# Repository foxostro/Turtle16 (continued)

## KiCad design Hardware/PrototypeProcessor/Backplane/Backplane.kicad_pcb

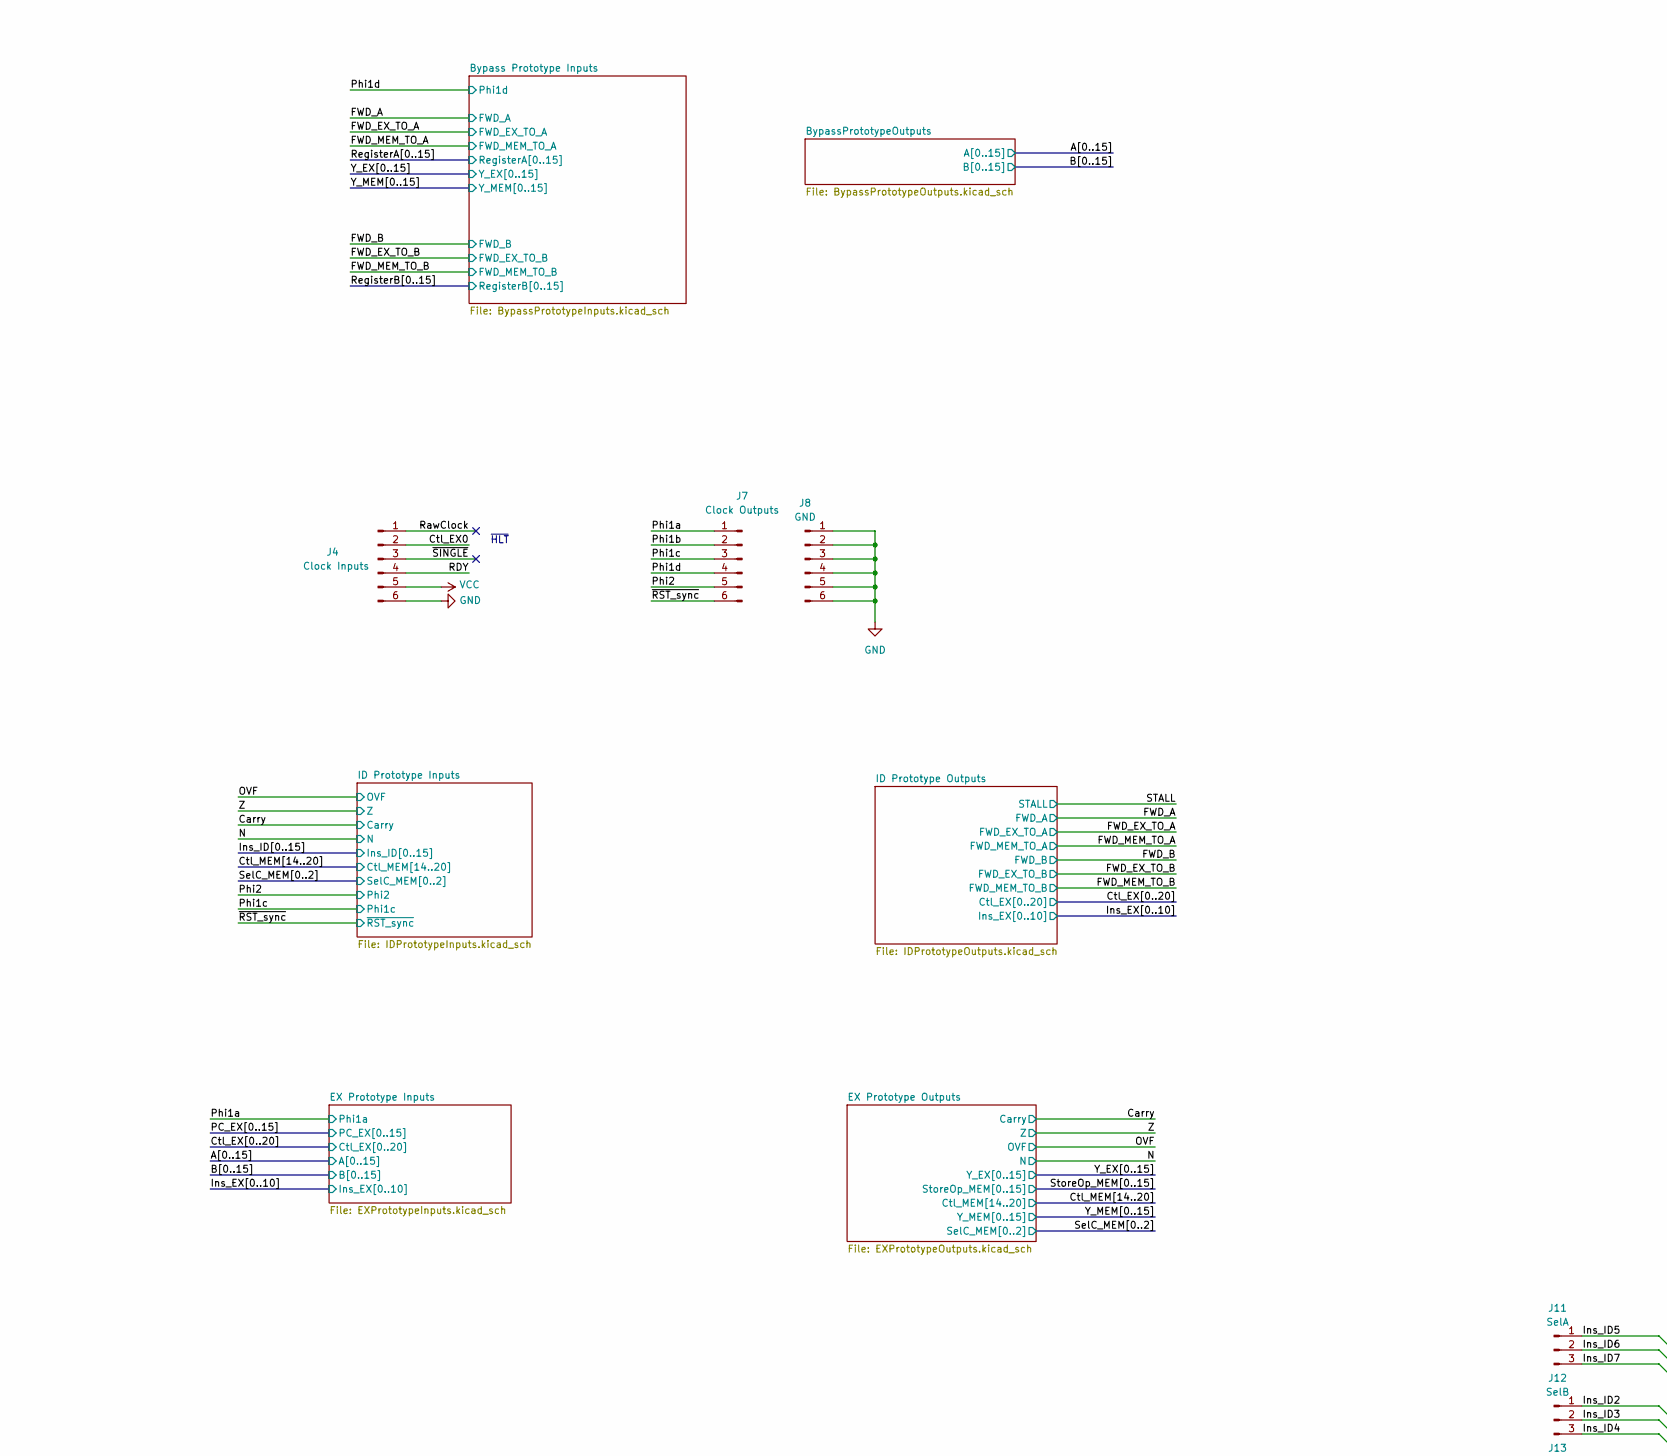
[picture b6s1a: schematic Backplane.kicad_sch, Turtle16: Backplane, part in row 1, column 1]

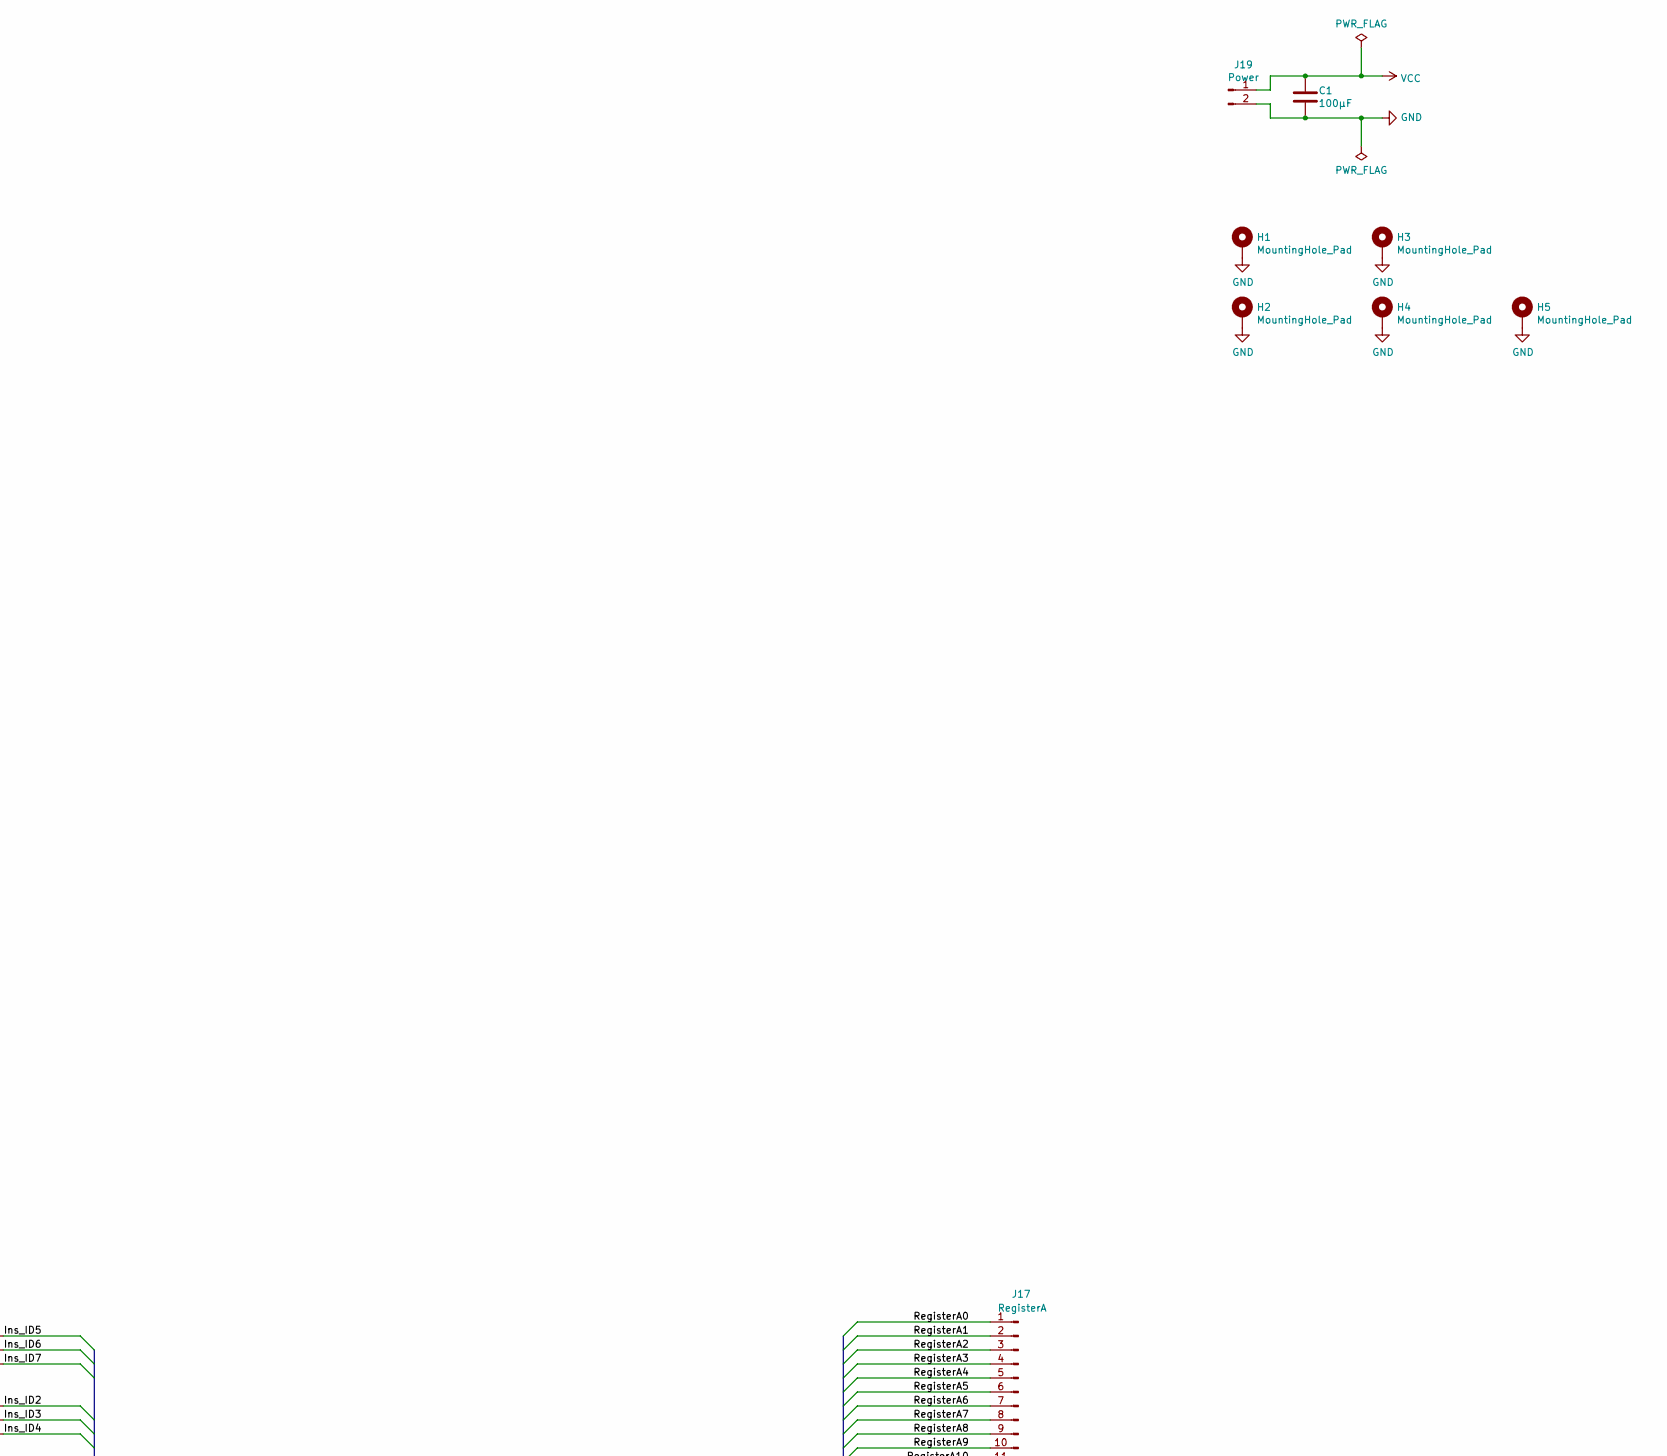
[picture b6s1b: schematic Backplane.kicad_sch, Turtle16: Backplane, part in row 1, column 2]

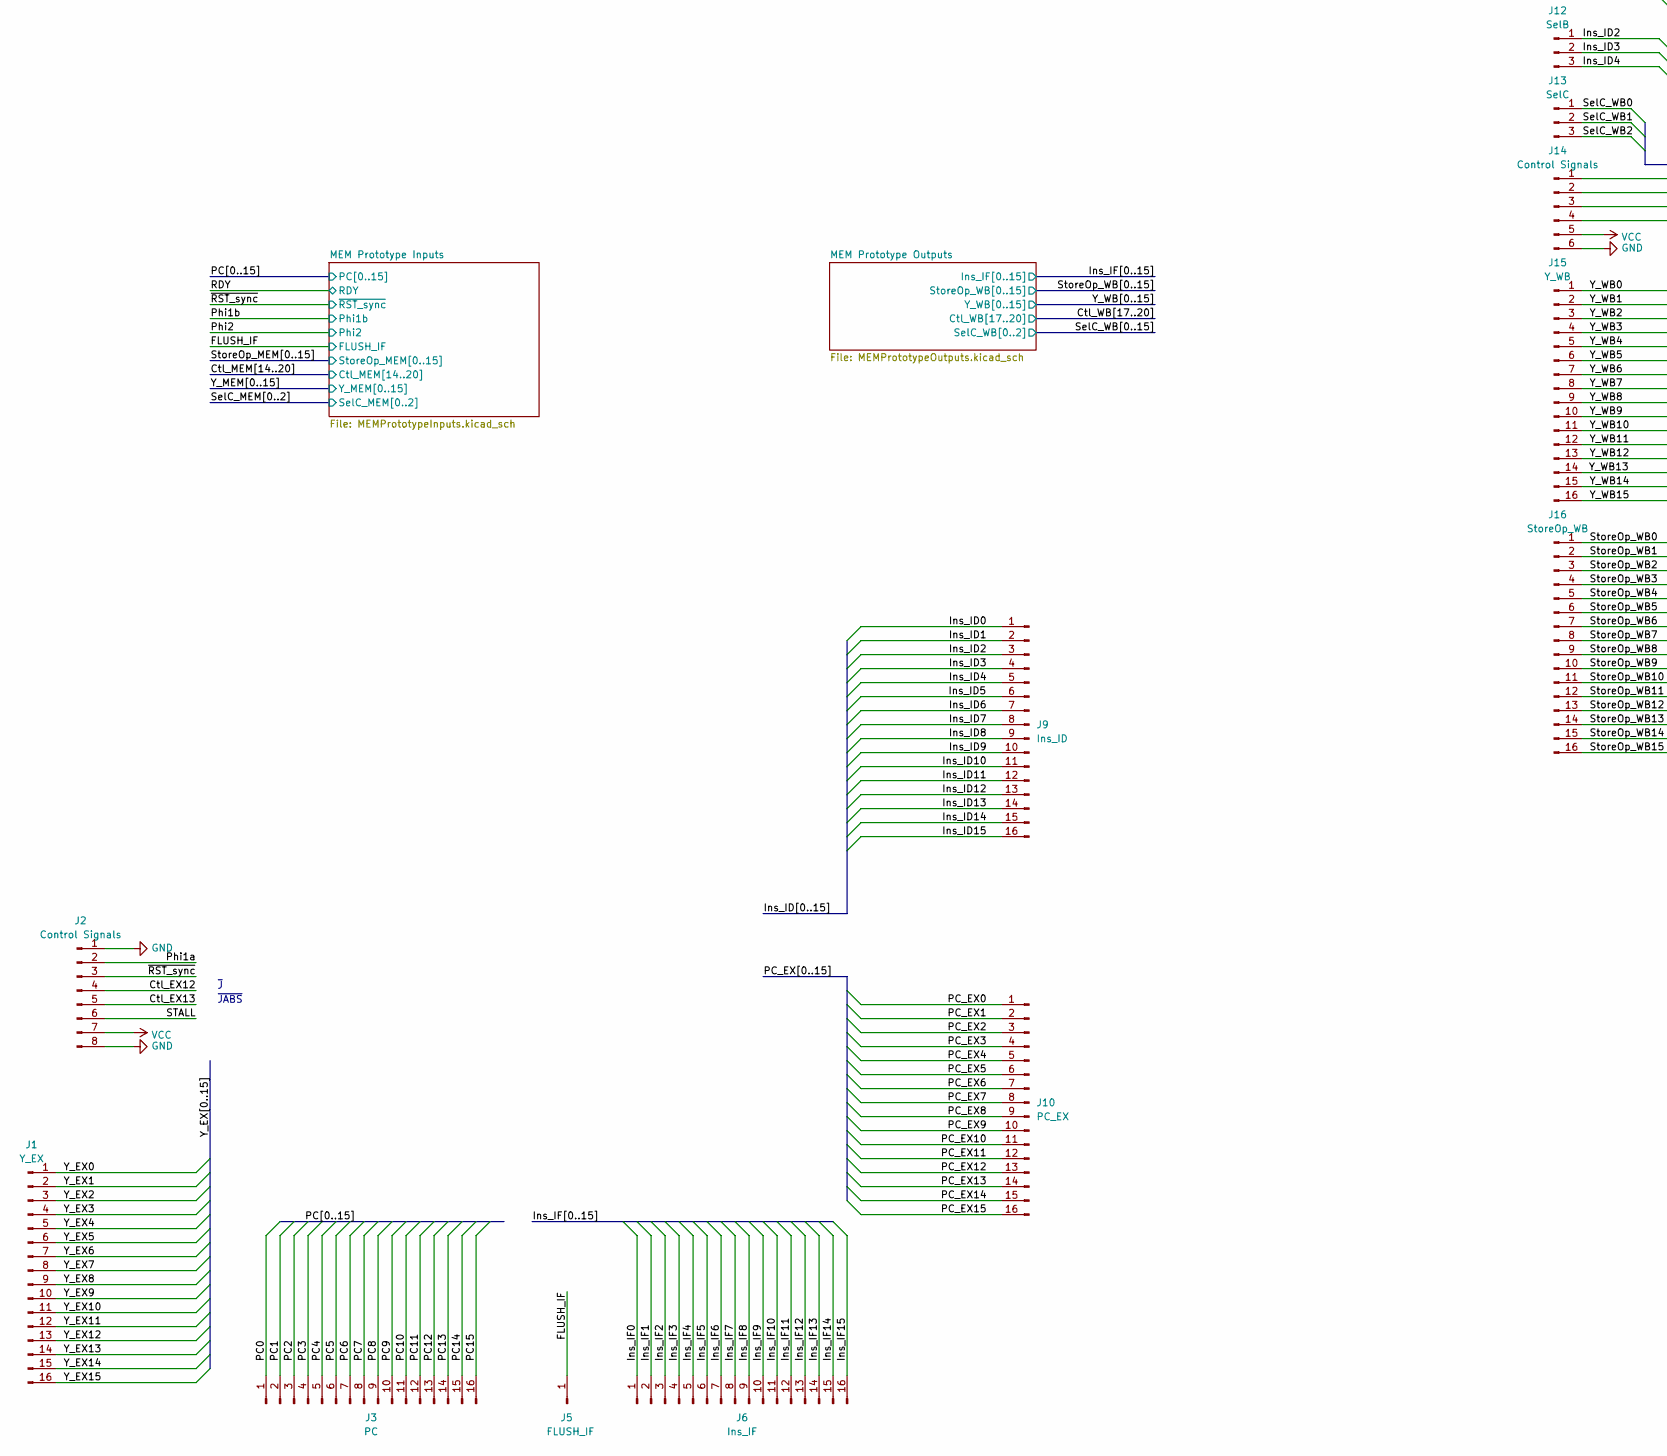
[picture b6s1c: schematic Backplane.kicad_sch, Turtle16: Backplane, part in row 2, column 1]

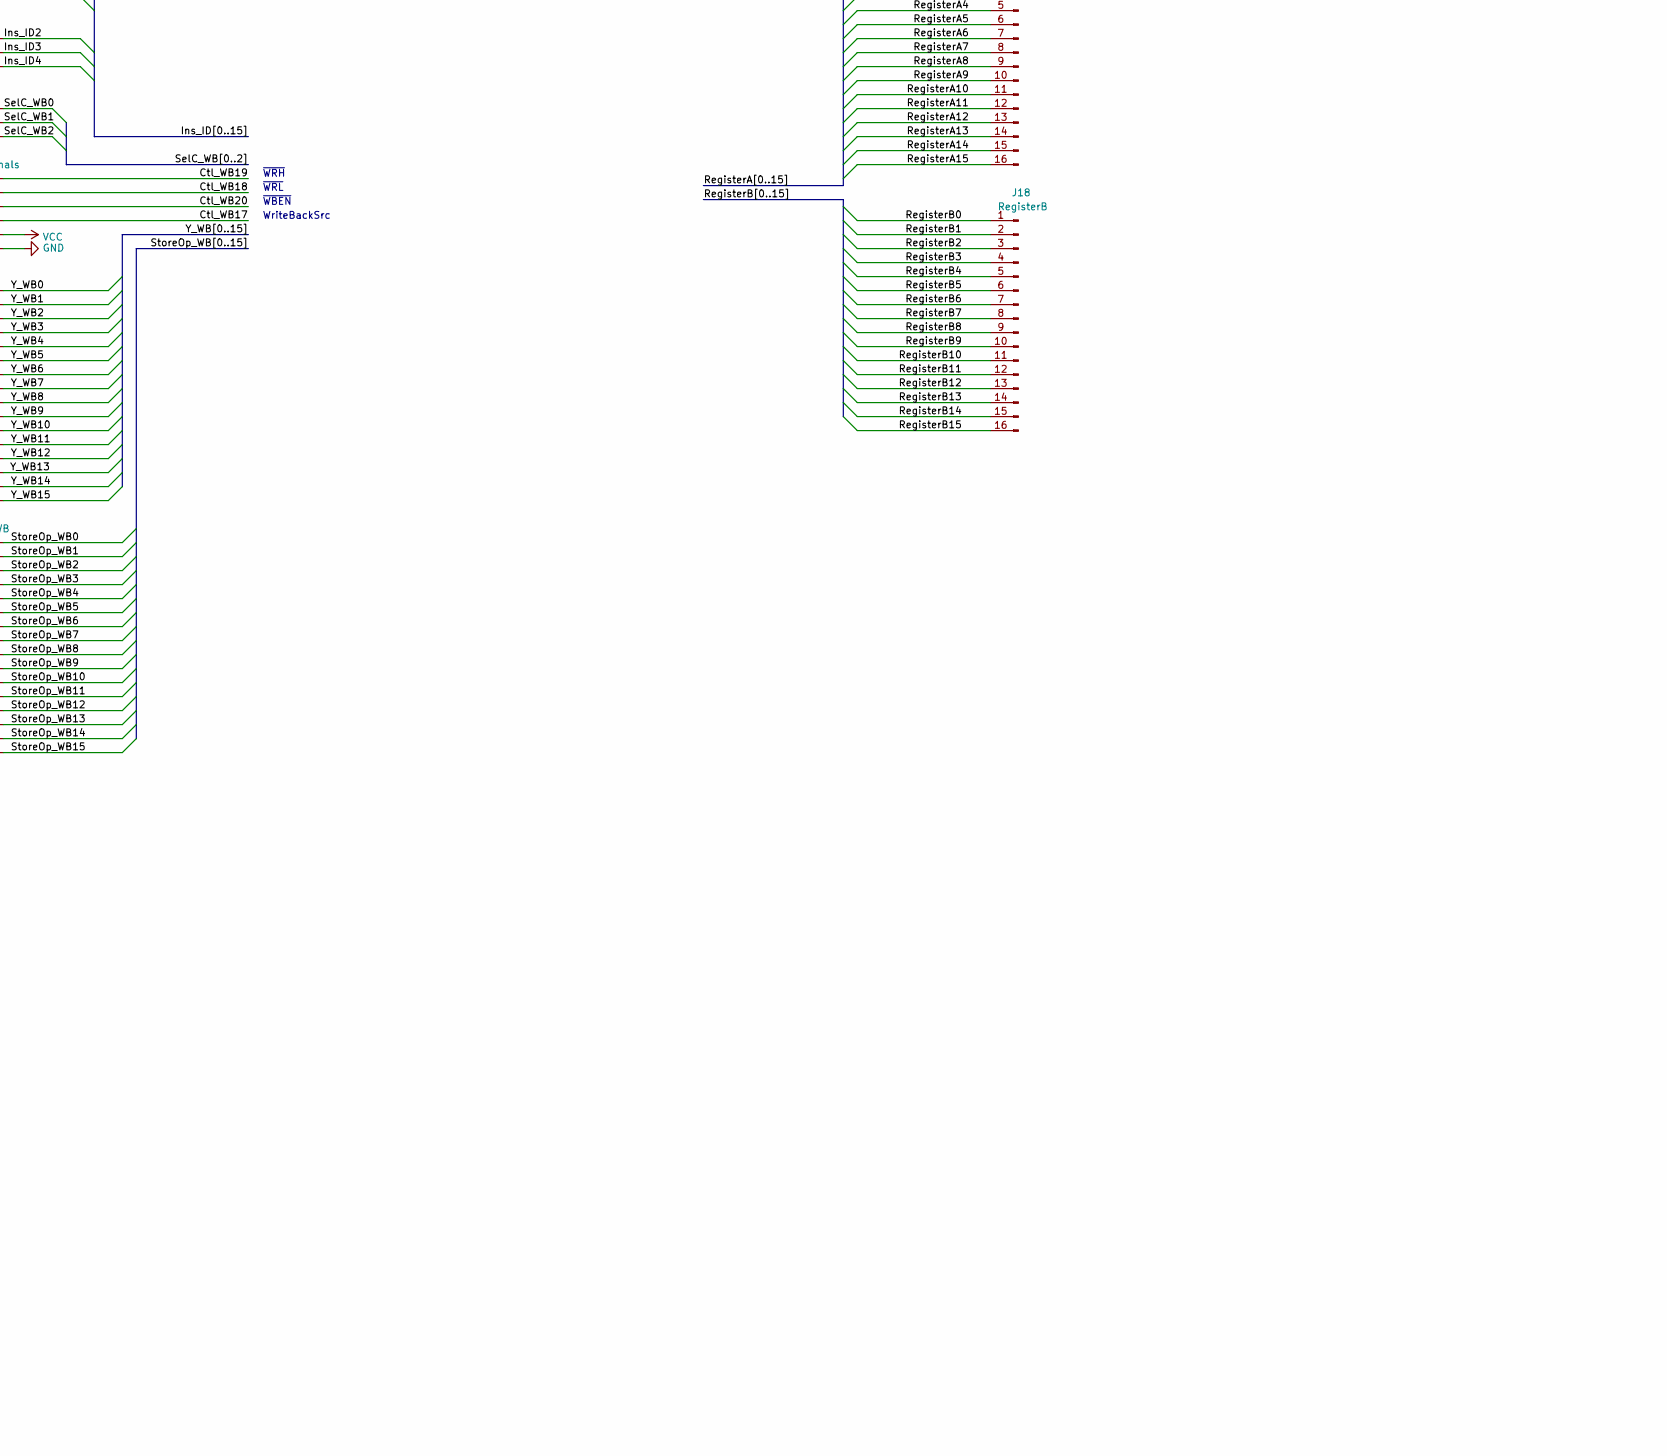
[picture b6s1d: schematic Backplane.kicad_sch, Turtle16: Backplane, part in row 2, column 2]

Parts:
C1: 100µF; C_1206_3216Metric_Pad1.33x1.80mm_HandSolder
H1, H2, H3, H4, H5: MountingHole_Pad; MountingHole_3.2mm_M3_Pad
J1: Y_EX; PinHeader_1x16_P2.54mm_Vertical
J2: Control Signals; PinHeader_1x08_P2.54mm_Vertical
J3: PC; PinHeader_1x16_P2.54mm_Vertical
J4: Clock Inputs; PinHeader_1x06_P2.54mm_Vertical
J5: FLUSH_IF; PinHeader_1x01_P2.54mm_Vertical
J6: Ins_IF; PinHeader_1x16_P2.54mm_Vertical
J7: Clock Outputs; PinHeader_1x06_P2.54mm_Vertical
J8: GND; PinHeader_1x06_P2.54mm_Vertical
J9: Ins_ID; PinHeader_1x16_P2.54mm_Vertical
J10: PC_EX; PinHeader_1x16_P2.54mm_Vertical
J11: SelA; PinHeader_1x03_P2.54mm_Vertical
J12: SelB; PinHeader_1x03_P2.54mm_Vertical
J13: SelC; PinHeader_1x03_P2.54mm_Vertical
J14: Control Signals; PinHeader_1x06_P2.54mm_Vertical
J15: Y_WB; PinHeader_1x16_P2.54mm_Vertical
J16: StoreOp_WB; PinHeader_1x16_P2.54mm_Vertical
J17: RegisterA; PinHeader_1x16_P2.54mm_Vertical
J18: RegisterB; PinHeader_1x16_P2.54mm_Vertical
J19: Power; 172448-0002

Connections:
/Ctl_EX0: J4.2; also elsewhere on the board
/Ctl_EX12: J2.4; also elsewhere on the board
/Ctl_EX13: J2.5; also elsewhere on the board
/Ctl_WB17: J14.4; also elsewhere on the board
/Ctl_WB18: J14.2; also elsewhere on the board
/Ctl_WB19: J14.1; also elsewhere on the board
/Ctl_WB20: J14.3; also elsewhere on the board
/FLUSH_IF: J5.1; also elsewhere on the board
/Ins_ID0: J9.1; also elsewhere on the board
/Ins_ID1: J9.2; also elsewhere on the board
/Ins_ID2: J9.3, J12.1; also elsewhere on the board
/Ins_ID3: J9.4, J12.2; also elsewhere on the board
/Ins_ID4: J9.5, J12.3; also elsewhere on the board
/Ins_ID5: J9.6, J11.1; also elsewhere on the board
/Ins_ID6: J9.7, J11.2; also elsewhere on the board
/Ins_ID7: J9.8, J11.3; also elsewhere on the board
/Ins_ID8: J9.9; also elsewhere on the board
/Ins_ID9: J9.10; also elsewhere on the board
/Ins_ID10: J9.11; also elsewhere on the board
/Ins_ID11: J9.12; also elsewhere on the board
/Ins_ID12: J9.13; also elsewhere on the board
/Ins_ID13: J9.14; also elsewhere on the board
/Ins_ID14: J9.15; also elsewhere on the board
/Ins_ID15: J9.16; also elsewhere on the board
/Ins_IF0: J6.1; also elsewhere on the board
/Ins_IF1: J6.2; also elsewhere on the board
/Ins_IF2: J6.3; also elsewhere on the board
/Ins_IF3: J6.4; also elsewhere on the board
/Ins_IF4: J6.5; also elsewhere on the board
/Ins_IF5: J6.6; also elsewhere on the board
/Ins_IF6: J6.7; also elsewhere on the board
/Ins_IF7: J6.8; also elsewhere on the board
/Ins_IF8: J6.9; also elsewhere on the board
/Ins_IF9: J6.10; also elsewhere on the board
/Ins_IF10: J6.11; also elsewhere on the board
/Ins_IF11: J6.12; also elsewhere on the board
/Ins_IF12: J6.13; also elsewhere on the board
/Ins_IF13: J6.14; also elsewhere on the board
/Ins_IF14: J6.15; also elsewhere on the board
/Ins_IF15: J6.16; also elsewhere on the board
/PC0: J3.1; also elsewhere on the board
/PC1: J3.2; also elsewhere on the board
/PC2: J3.3; also elsewhere on the board
/PC3: J3.4; also elsewhere on the board
/PC4: J3.5; also elsewhere on the board
/PC5: J3.6; also elsewhere on the board
/PC6: J3.7; also elsewhere on the board
/PC7: J3.8; also elsewhere on the board
/PC8: J3.9; also elsewhere on the board
/PC9: J3.10; also elsewhere on the board
/PC10: J3.11; also elsewhere on the board
/PC11: J3.12; also elsewhere on the board
/PC12: J3.13; also elsewhere on the board
/PC13: J3.14; also elsewhere on the board
/PC14: J3.15; also elsewhere on the board
/PC15: J3.16; also elsewhere on the board
/PC_EX0: J10.1; also elsewhere on the board
/PC_EX1: J10.2; also elsewhere on the board
/PC_EX2: J10.3; also elsewhere on the board
/PC_EX3: J10.4; also elsewhere on the board
/PC_EX4: J10.5; also elsewhere on the board
/PC_EX5: J10.6; also elsewhere on the board
/PC_EX6: J10.7; also elsewhere on the board
/PC_EX7: J10.8; also elsewhere on the board
/PC_EX8: J10.9; also elsewhere on the board
/PC_EX9: J10.10; also elsewhere on the board
/PC_EX10: J10.11; also elsewhere on the board
/PC_EX11: J10.12; also elsewhere on the board
/PC_EX12: J10.13; also elsewhere on the board
/PC_EX13: J10.14; also elsewhere on the board
/PC_EX14: J10.15; also elsewhere on the board
/PC_EX15: J10.16; also elsewhere on the board
/Phi1a: J2.2, J7.1; also elsewhere on the board
/Phi1b: J7.2; also elsewhere on the board
/Phi1c: J7.3; also elsewhere on the board
/Phi1d: J7.4; also elsewhere on the board
/Phi2: J7.5; also elsewhere on the board
/RDY: J4.4; also elsewhere on the board
/RawClock: J4.1
/RegisterA0: J17.1; also elsewhere on the board
/RegisterA1: J17.2; also elsewhere on the board
/RegisterA2: J17.3; also elsewhere on the board
/RegisterA3: J17.4; also elsewhere on the board
/RegisterA4: J17.5; also elsewhere on the board
/RegisterA5: J17.6; also elsewhere on the board
/RegisterA6: J17.7; also elsewhere on the board
/RegisterA7: J17.8; also elsewhere on the board
/RegisterA8: J17.9; also elsewhere on the board
/RegisterA9: J17.10; also elsewhere on the board
/RegisterA10: J17.11; also elsewhere on the board
/RegisterA11: J17.12; also elsewhere on the board
/RegisterA12: J17.13; also elsewhere on the board
/RegisterA13: J17.14; also elsewhere on the board
/RegisterA14: J17.15; also elsewhere on the board
/RegisterA15: J17.16; also elsewhere on the board
/RegisterB0: J18.1; also elsewhere on the board
/RegisterB1: J18.2; also elsewhere on the board
/RegisterB2: J18.3; also elsewhere on the board
/RegisterB3: J18.4; also elsewhere on the board
/RegisterB4: J18.5; also elsewhere on the board
/RegisterB5: J18.6; also elsewhere on the board
/RegisterB6: J18.7; also elsewhere on the board
/RegisterB7: J18.8; also elsewhere on the board
/RegisterB8: J18.9; also elsewhere on the board
/RegisterB9: J18.10; also elsewhere on the board
/RegisterB10: J18.11; also elsewhere on the board
/RegisterB11: J18.12; also elsewhere on the board
/RegisterB12: J18.13; also elsewhere on the board
/RegisterB13: J18.14; also elsewhere on the board
/RegisterB14: J18.15; also elsewhere on the board
/RegisterB15: J18.16; also elsewhere on the board
/STALL: J2.6; also elsewhere on the board
/SelC_WB0: J13.1; also elsewhere on the board
/SelC_WB1: J13.2; also elsewhere on the board
/SelC_WB2: J13.3; also elsewhere on the board
/StoreOp_WB0: J16.1; also elsewhere on the board
/StoreOp_WB1: J16.2; also elsewhere on the board
/StoreOp_WB2: J16.3; also elsewhere on the board
/StoreOp_WB3: J16.4; also elsewhere on the board
/StoreOp_WB4: J16.5; also elsewhere on the board
/StoreOp_WB5: J16.6; also elsewhere on the board
/StoreOp_WB6: J16.7; also elsewhere on the board
/StoreOp_WB7: J16.8; also elsewhere on the board
/StoreOp_WB8: J16.9; also elsewhere on the board
/StoreOp_WB9: J16.10; also elsewhere on the board
/StoreOp_WB10: J16.11; also elsewhere on the board
/StoreOp_WB11: J16.12; also elsewhere on the board
/StoreOp_WB12: J16.13; also elsewhere on the board
/StoreOp_WB13: J16.14; also elsewhere on the board
/StoreOp_WB14: J16.15; also elsewhere on the board
/StoreOp_WB15: J16.16; also elsewhere on the board
/Y_EX0: J1.1; also elsewhere on the board
/Y_EX1: J1.2; also elsewhere on the board
/Y_EX2: J1.3; also elsewhere on the board
/Y_EX3: J1.4; also elsewhere on the board
/Y_EX4: J1.5; also elsewhere on the board
/Y_EX5: J1.6; also elsewhere on the board
/Y_EX6: J1.7; also elsewhere on the board
/Y_EX7: J1.8; also elsewhere on the board
/Y_EX8: J1.9; also elsewhere on the board
/Y_EX9: J1.10; also elsewhere on the board
/Y_EX10: J1.11; also elsewhere on the board
/Y_EX11: J1.12; also elsewhere on the board
/Y_EX12: J1.13; also elsewhere on the board
/Y_EX13: J1.14; also elsewhere on the board
/Y_EX14: J1.15; also elsewhere on the board
/Y_EX15: J1.16; also elsewhere on the board
/Y_WB0: J15.1; also elsewhere on the board
/Y_WB1: J15.2; also elsewhere on the board
/Y_WB2: J15.3; also elsewhere on the board
/Y_WB3: J15.4; also elsewhere on the board
/Y_WB4: J15.5; also elsewhere on the board
/Y_WB5: J15.6; also elsewhere on the board
/Y_WB6: J15.7; also elsewhere on the board
/Y_WB7: J15.8; also elsewhere on the board
/Y_WB8: J15.9; also elsewhere on the board
/Y_WB9: J15.10; also elsewhere on the board
/Y_WB10: J15.11; also elsewhere on the board
/Y_WB11: J15.12; also elsewhere on the board
/Y_WB12: J15.13; also elsewhere on the board
/Y_WB13: J15.14; also elsewhere on the board
/Y_WB14: J15.15; also elsewhere on the board
/Y_WB15: J15.16; also elsewhere on the board
/~RST_sync: J2.3, J7.6; also elsewhere on the board
/~SINGLE: J4.3
GND: C1.2, H1.1, H2.1, H3.1, H4.1, H5.1, J2.1, J2.8, J4.6, J8.1, J8.2, J8.3, J8.4, J8.5, J8.6, J14.6, J19.2; also elsewhere on the board
VCC: C1.1, J2.7, J4.5, J14.5, J19.1; also elsewhere on the board

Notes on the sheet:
~{JABS}
~{HLT}
~{WBEN}
~{WRL}
~{WRH}
WriteBackSrc
~{J}

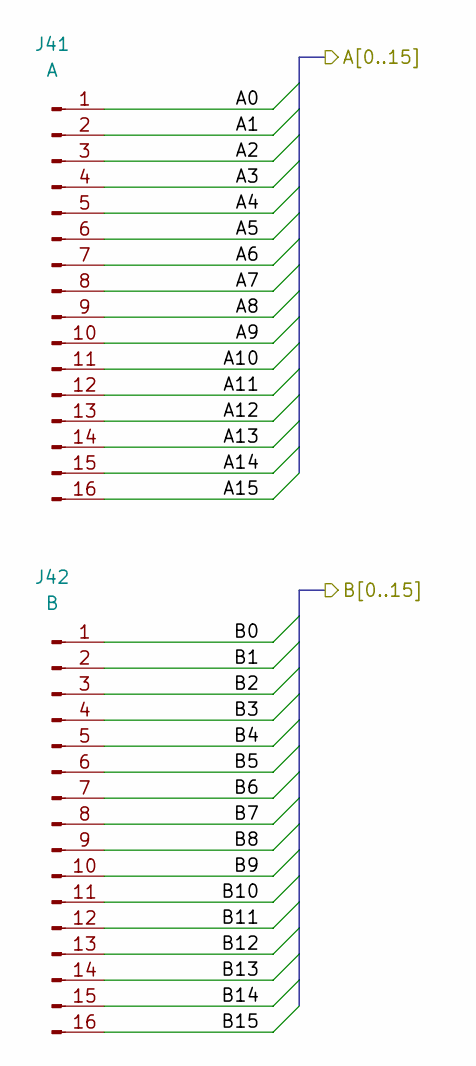
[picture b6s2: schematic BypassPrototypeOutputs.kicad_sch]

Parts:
J41: A; PinHeader_1x16_P2.54mm_Vertical
J42: B; PinHeader_1x16_P2.54mm_Vertical

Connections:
/A0: J41.1; also elsewhere on the board
/A1: J41.2; also elsewhere on the board
/A2: J41.3; also elsewhere on the board
/A3: J41.4; also elsewhere on the board
/A4: J41.5; also elsewhere on the board
/A5: J41.6; also elsewhere on the board
/A6: J41.7; also elsewhere on the board
/A7: J41.8; also elsewhere on the board
/A8: J41.9; also elsewhere on the board
/A9: J41.10; also elsewhere on the board
/A10: J41.11; also elsewhere on the board
/A11: J41.12; also elsewhere on the board
/A12: J41.13; also elsewhere on the board
/A13: J41.14; also elsewhere on the board
/A14: J41.15; also elsewhere on the board
/A15: J41.16; also elsewhere on the board
/B0: J42.1; also elsewhere on the board
/B1: J42.2; also elsewhere on the board
/B2: J42.3; also elsewhere on the board
/B3: J42.4; also elsewhere on the board
/B4: J42.5; also elsewhere on the board
/B5: J42.6; also elsewhere on the board
/B6: J42.7; also elsewhere on the board
/B7: J42.8; also elsewhere on the board
/B8: J42.9; also elsewhere on the board
/B9: J42.10; also elsewhere on the board
/B10: J42.11; also elsewhere on the board
/B11: J42.12; also elsewhere on the board
/B12: J42.13; also elsewhere on the board
/B13: J42.14; also elsewhere on the board
/B14: J42.15; also elsewhere on the board
/B15: J42.16; also elsewhere on the board

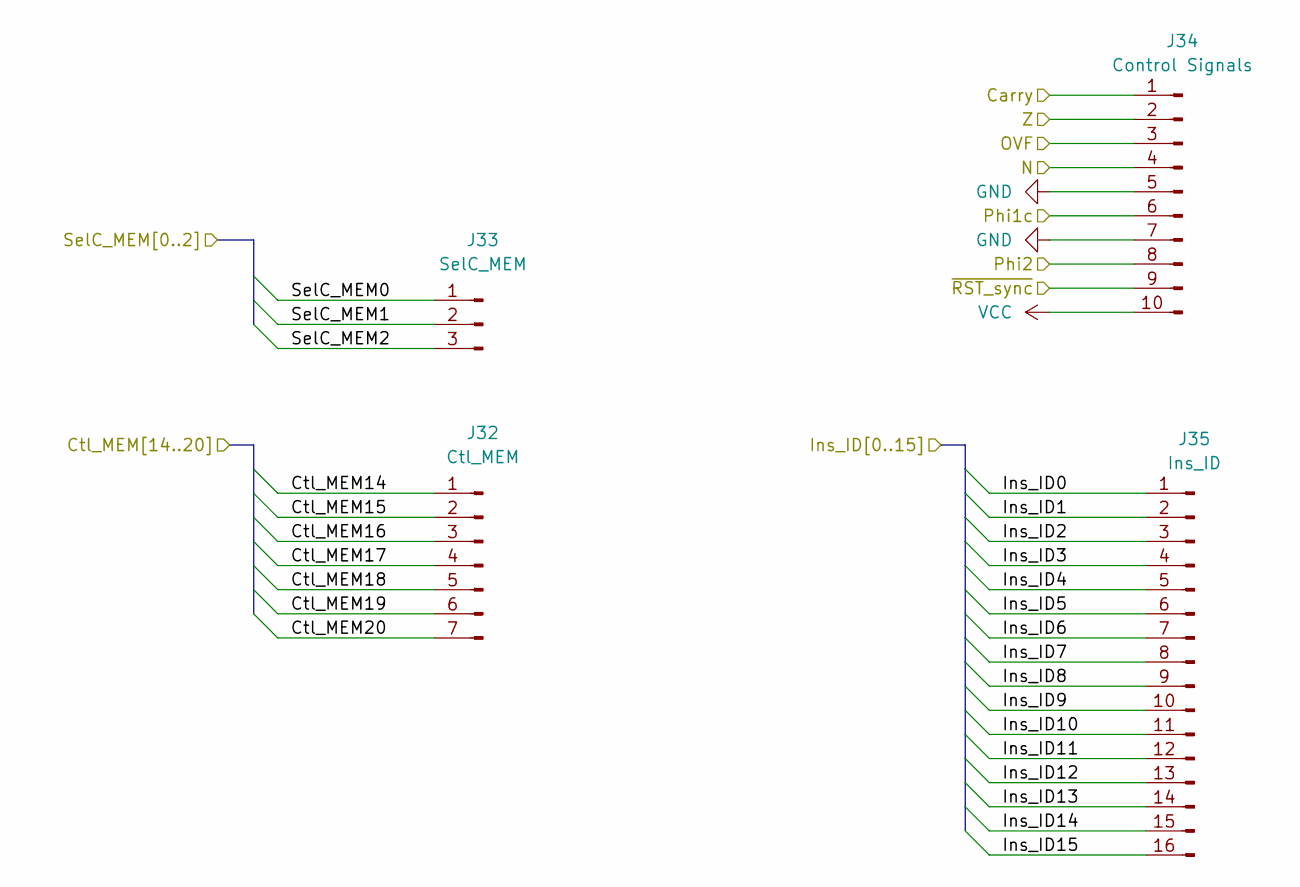
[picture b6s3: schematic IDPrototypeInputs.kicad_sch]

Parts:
J32: Ctl_MEM; PinHeader_1x07_P2.54mm_Vertical
J33: SelC_MEM; PinHeader_1x03_P2.54mm_Vertical
J34: Control Signals; PinHeader_1x10_P2.54mm_Vertical
J35: Ins_ID; PinHeader_1x16_P2.54mm_Vertical

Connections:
/Carry: J34.1; also elsewhere on the board
/Ctl_MEM14: J32.1; also elsewhere on the board
/Ctl_MEM15: J32.2; also elsewhere on the board
/Ctl_MEM16: J32.3; also elsewhere on the board
/Ctl_MEM17: J32.4; also elsewhere on the board
/Ctl_MEM18: J32.5; also elsewhere on the board
/Ctl_MEM19: J32.6; also elsewhere on the board
/Ctl_MEM20: J32.7; also elsewhere on the board
/Ins_ID0: J35.1; also elsewhere on the board
/Ins_ID1: J35.2; also elsewhere on the board
/Ins_ID2: J35.3; also elsewhere on the board
/Ins_ID3: J35.4; also elsewhere on the board
/Ins_ID4: J35.5; also elsewhere on the board
/Ins_ID5: J35.6; also elsewhere on the board
/Ins_ID6: J35.7; also elsewhere on the board
/Ins_ID7: J35.8; also elsewhere on the board
/Ins_ID8: J35.9; also elsewhere on the board
/Ins_ID9: J35.10; also elsewhere on the board
/Ins_ID10: J35.11; also elsewhere on the board
/Ins_ID11: J35.12; also elsewhere on the board
/Ins_ID12: J35.13; also elsewhere on the board
/Ins_ID13: J35.14; also elsewhere on the board
/Ins_ID14: J35.15; also elsewhere on the board
/Ins_ID15: J35.16; also elsewhere on the board
/N: J34.4; also elsewhere on the board
/OVF: J34.3; also elsewhere on the board
/Phi1c: J34.6; also elsewhere on the board
/Phi2: J34.8; also elsewhere on the board
/SelC_MEM0: J33.1; also elsewhere on the board
/SelC_MEM1: J33.2; also elsewhere on the board
/SelC_MEM2: J33.3; also elsewhere on the board
/Z: J34.2; also elsewhere on the board
/~RST_sync: J34.9; also elsewhere on the board
GND: J34.5, J34.7; also elsewhere on the board
VCC: J34.10; also elsewhere on the board

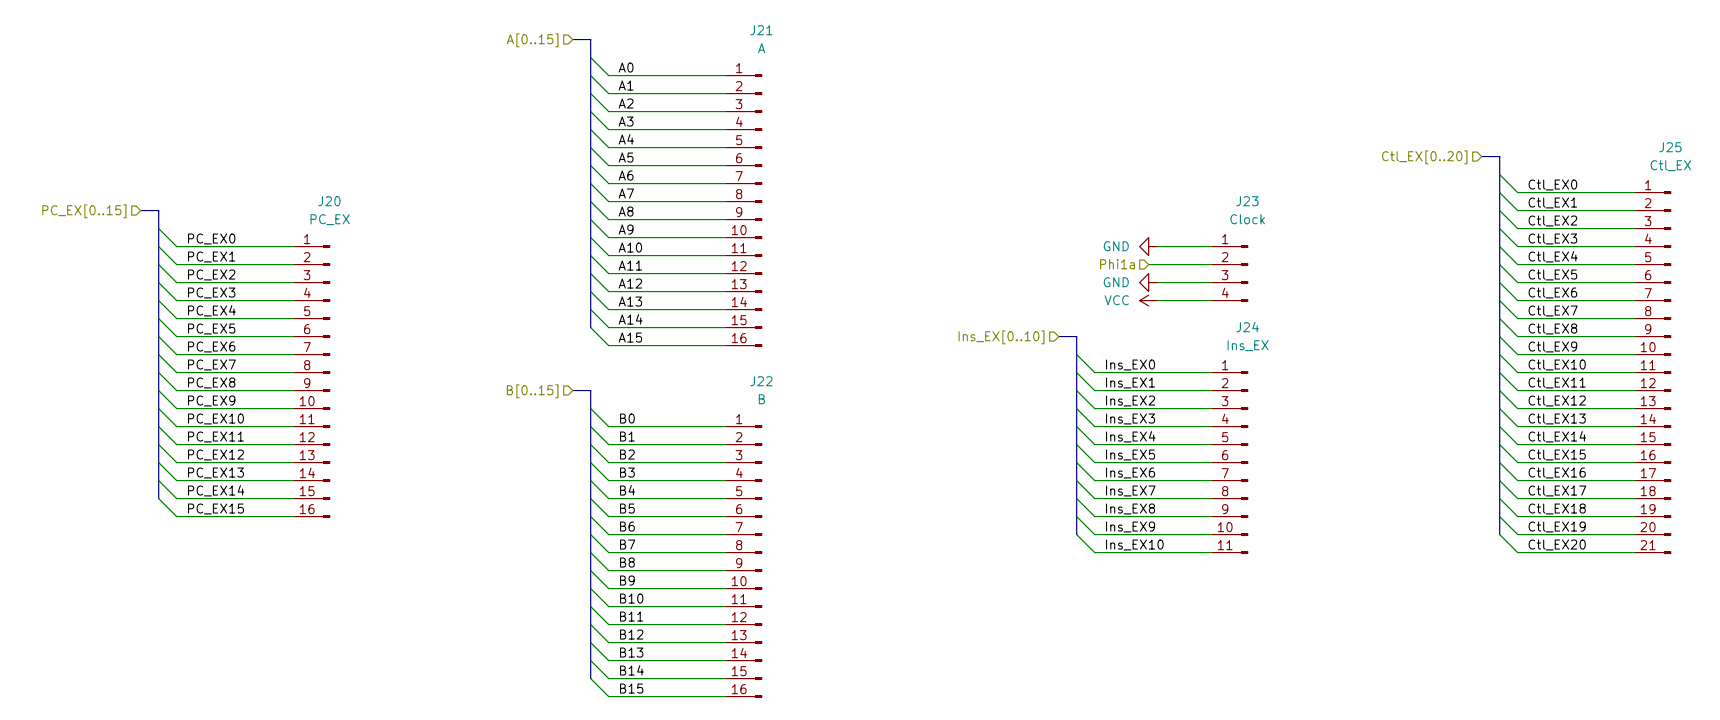
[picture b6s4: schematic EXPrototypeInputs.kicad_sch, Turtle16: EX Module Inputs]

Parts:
J20: PC_EX; PinHeader_1x16_P2.54mm_Vertical
J21: A; PinHeader_1x16_P2.54mm_Vertical
J22: B; PinHeader_1x16_P2.54mm_Vertical
J23: Clock; PinHeader_1x04_P2.54mm_Vertical
J24: Ins_EX; PinHeader_1x11_P2.54mm_Vertical
J25: Ctl_EX; PinHeader_1x21_P2.54mm_Vertical

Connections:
/A0: J21.1; also elsewhere on the board
/A1: J21.2; also elsewhere on the board
/A2: J21.3; also elsewhere on the board
/A3: J21.4; also elsewhere on the board
/A4: J21.5; also elsewhere on the board
/A5: J21.6; also elsewhere on the board
/A6: J21.7; also elsewhere on the board
/A7: J21.8; also elsewhere on the board
/A8: J21.9; also elsewhere on the board
/A9: J21.10; also elsewhere on the board
/A10: J21.11; also elsewhere on the board
/A11: J21.12; also elsewhere on the board
/A12: J21.13; also elsewhere on the board
/A13: J21.14; also elsewhere on the board
/A14: J21.15; also elsewhere on the board
/A15: J21.16; also elsewhere on the board
/B0: J22.1; also elsewhere on the board
/B1: J22.2; also elsewhere on the board
/B2: J22.3; also elsewhere on the board
/B3: J22.4; also elsewhere on the board
/B4: J22.5; also elsewhere on the board
/B5: J22.6; also elsewhere on the board
/B6: J22.7; also elsewhere on the board
/B7: J22.8; also elsewhere on the board
/B8: J22.9; also elsewhere on the board
/B9: J22.10; also elsewhere on the board
/B10: J22.11; also elsewhere on the board
/B11: J22.12; also elsewhere on the board
/B12: J22.13; also elsewhere on the board
/B13: J22.14; also elsewhere on the board
/B14: J22.15; also elsewhere on the board
/B15: J22.16; also elsewhere on the board
/Ctl_EX0: J25.1; also elsewhere on the board
/Ctl_EX1: J25.2; also elsewhere on the board
/Ctl_EX2: J25.3; also elsewhere on the board
/Ctl_EX3: J25.4; also elsewhere on the board
/Ctl_EX4: J25.5; also elsewhere on the board
/Ctl_EX5: J25.6; also elsewhere on the board
/Ctl_EX6: J25.7; also elsewhere on the board
/Ctl_EX7: J25.8; also elsewhere on the board
/Ctl_EX8: J25.9; also elsewhere on the board
/Ctl_EX9: J25.10; also elsewhere on the board
/Ctl_EX10: J25.11; also elsewhere on the board
/Ctl_EX11: J25.12; also elsewhere on the board
/Ctl_EX12: J25.13; also elsewhere on the board
/Ctl_EX13: J25.14; also elsewhere on the board
/Ctl_EX14: J25.15; also elsewhere on the board
/Ctl_EX15: J25.16; also elsewhere on the board
/Ctl_EX16: J25.17; also elsewhere on the board
/Ctl_EX17: J25.18; also elsewhere on the board
/Ctl_EX18: J25.19; also elsewhere on the board
/Ctl_EX19: J25.20; also elsewhere on the board
/Ctl_EX20: J25.21; also elsewhere on the board
/Ins_EX0: J24.1; also elsewhere on the board
/Ins_EX1: J24.2; also elsewhere on the board
/Ins_EX2: J24.3; also elsewhere on the board
/Ins_EX3: J24.4; also elsewhere on the board
/Ins_EX4: J24.5; also elsewhere on the board
/Ins_EX5: J24.6; also elsewhere on the board
/Ins_EX6: J24.7; also elsewhere on the board
/Ins_EX7: J24.8; also elsewhere on the board
/Ins_EX8: J24.9; also elsewhere on the board
/Ins_EX9: J24.10; also elsewhere on the board
/Ins_EX10: J24.11; also elsewhere on the board
/PC_EX0: J20.1; also elsewhere on the board
/PC_EX1: J20.2; also elsewhere on the board
/PC_EX2: J20.3; also elsewhere on the board
/PC_EX3: J20.4; also elsewhere on the board
/PC_EX4: J20.5; also elsewhere on the board
/PC_EX5: J20.6; also elsewhere on the board
/PC_EX6: J20.7; also elsewhere on the board
/PC_EX7: J20.8; also elsewhere on the board
/PC_EX8: J20.9; also elsewhere on the board
/PC_EX9: J20.10; also elsewhere on the board
/PC_EX10: J20.11; also elsewhere on the board
/PC_EX11: J20.12; also elsewhere on the board
/PC_EX12: J20.13; also elsewhere on the board
/PC_EX13: J20.14; also elsewhere on the board
/PC_EX14: J20.15; also elsewhere on the board
/PC_EX15: J20.16; also elsewhere on the board
/Phi1a: J23.2; also elsewhere on the board
GND: J23.1, J23.3; also elsewhere on the board
VCC: J23.4; also elsewhere on the board
